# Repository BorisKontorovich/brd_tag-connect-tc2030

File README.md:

## Breakout board for Tag Connect tc2030 cable

This might be a handy accessory for those who want to program and debug PIC microcontrollers using ICD 4 or ICD 3.

You can buy the cable through DigiKey or other suppliers. [Link](https://www.digikey.com/products/en/development-boards-kits-programmers/accessories/783?k=&pkeyword=&pv184=1270&FV=ffe0030f%2Cfffc0096&quantity=0&ColumnSort=0&page=1&stock=1&datasheet=1&pageSize=500)

You can check out manufacturers website here. [Link](http://www.tag-connect.com/)

Here is a link to Microchip ICD 4 [Link](pagehttp://www.microchip.com/Developmenttools/ProductDetails.aspx?PartNO=DV164045)

You can get these made using OshPark. Their pricing and delivery times are very reasonable. [Link](http:oshpark.com)

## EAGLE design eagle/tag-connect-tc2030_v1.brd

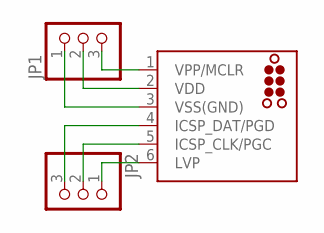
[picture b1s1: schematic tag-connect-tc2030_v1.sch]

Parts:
JP1, JP2: PINHD-1X3; 1X03
TAG-CONN: TC2030-MCP

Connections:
ICSP_CLK/PGC: JP2.2, TAG-CONN.5 (ICSP_CLK/PGC)
ICSP_DAT/PGD: JP2.3, TAG-CONN.4 (ICSP_DAT/PGD)
LVP: JP2.1, TAG-CONN.6 (LVP)
VDD: JP1.2, TAG-CONN.2 (VDD)
VPP/MCLR: JP1.3, TAG-CONN.1 (VPP/MCLR)
VSS(GND): JP1.1, TAG-CONN.3 (VSS(GND))

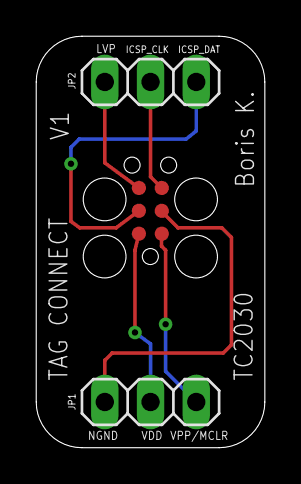
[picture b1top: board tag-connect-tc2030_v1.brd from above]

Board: 2 copper layers, 12.7 x 22.9 mm, 3 parts (0 on the bottom side), 6 nets.

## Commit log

2018-04-14 Initial file add.
2018-04-15 Added datasheets and updated readme.
2018-04-15 Updateing readme

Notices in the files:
parts and their libraries:
tag-connect: ©2009 ROFA.cz - modified and updated by Robert Darlington ‹rdarlington@gmail.com›
